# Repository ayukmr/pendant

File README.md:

# pendant

Pendant with a charlieplexed LED matrix using an ATSAMD21.

## Demo

## Schematic

## PCB

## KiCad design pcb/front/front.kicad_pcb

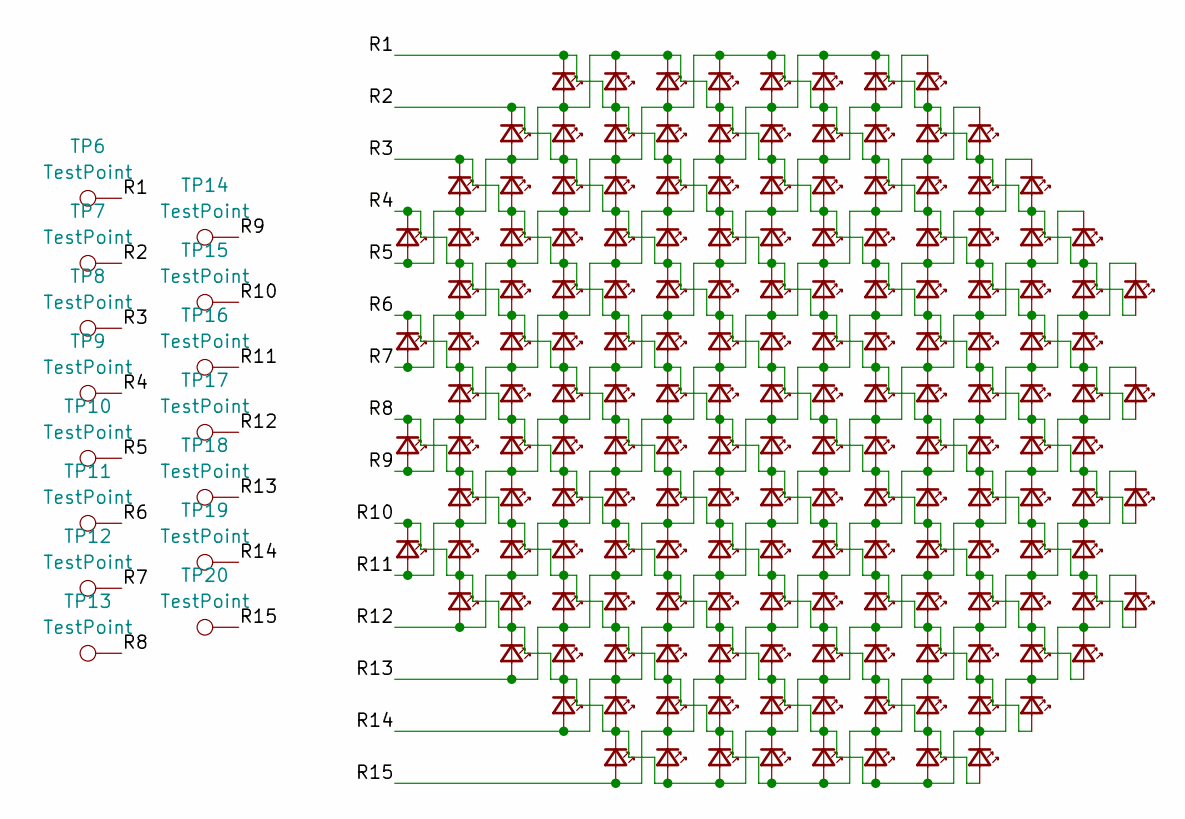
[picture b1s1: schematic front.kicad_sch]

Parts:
D1, D2, D3, D4, D5, D6, D7, D8, D9, D10, D11, D12, D13, D14, D15, D16, D17, D18, D19, D20, D21, D22, D23, D24, D25, D26, D27, D28, D29, D30, D31, D32, D33, D34, D35, D36, D37, D38, D39, D40, D41, D42, D43, D44, D45, D46, D47, D48, D49, D50, D51, D52, D53, D54, D55, D56, D57, D58, D59, D60, D61, D62, D63, D64, D65, D66, D67, D68, D69, D70, D71, D72, D73, D74, D75, D76, D77, D78, D79, D80, D81, D82, D83, D84, D85, D86, D87, D88, D89, D90, D91, D92, D93, D94, D95, D96, D97, D98, D99, D100, D101, D102, D103, D104, D105, D106, D107, D108, D109, D110, D111, D112, D113, D114, D115, D116, D117, D118, D119, D120, D121, D122, D123, D124, D125, D126, D127, D128, D129, D130, D131, D132, D133, D134, D135, D136, D137, D138, D139, D140, D141, D142, D143, D144, D145, D146, D147, D148, D149, D150, D151, D152, D153, D154, D155, D156, D157, D158, D159, D160, D161, D162, D163, D164, D165, D166, D167, D168, D169, D170, D171, D172: LED_Small; LED_0402_1005Metric
TP6, TP7, TP8, TP9, TP10, TP11, TP12, TP13, TP14, TP15, TP16, TP17, TP18, TP19, TP20: TestPoint; Pad_SMD_1.6x1.6

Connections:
/R1: D1.1 (K), D2.2 (A), D11.1 (K), D12.2 (A), D23.1 (K), D24.2 (A), D37.1 (K), D38.2 (A), D51.1 (K), D52.2 (A), D67.1 (K), D68.2 (A), D81.1 (K), D82.2 (A), D97.1 (K), D98.2 (A), D111.1 (K), D112.2 (A), D127.1 (K), D128.2 (A), D141.1 (K), D142.2 (A), TP6.1 (1_1)
/R2: D9.1 (K), D10.2 (A), D21.1 (K), D22.2 (A), D35.1 (K), D36.2 (A), D49.1 (K), D50.2 (A), D65.1 (K), D66.2 (A), D79.1 (K), D80.2 (A), D95.1 (K), D96.2 (A), D109.1 (K), D110.2 (A), D125.1 (K), D126.2 (A), D139.1 (K), D140.2 (A), D153.1 (K), D154.2 (A), TP7.1 (1_1)
/R3: D19.1 (K), D20.2 (A), D33.1 (K), D34.2 (A), D47.1 (K), D48.2 (A), D63.1 (K), D64.2 (A), D77.1 (K), D78.2 (A), D93.1 (K), D94.2 (A), D107.1 (K), D108.2 (A), D123.1 (K), D124.2 (A), D137.1 (K), D138.2 (A), D151.1 (K), D152.2 (A), D163.1 (K), D164.2 (A), TP8.1 (1_1)
/R4: D31.1 (K), D32.2 (A), D45.1 (K), D46.2 (A), D61.1 (K), D62.2 (A), D75.1 (K), D76.2 (A), D91.1 (K), D92.2 (A), D105.1 (K), D106.2 (A), D121.1 (K), D122.2 (A), D135.1 (K), D136.2 (A), D149.1 (K), D150.2 (A), D161.1 (K), D162.2 (A), D171.1 (K), D172.2 (A), TP9.1 (1_1)
/R5: D1.2 (A), D2.1 (K), D3.1 (K), D4.2 (A), D9.2 (A), D10.1 (K), D13.1 (K), D14.2 (A), D19.2 (A), D20.1 (K), D25.1 (K), D26.2 (A), D31.2 (A), D32.1 (K), D39.1 (K), D40.2 (A), D53.1 (K), D54.2 (A), D69.1 (K), D70.2 (A), D83.1 (K), D84.2 (A), D99.1 (K), D100.2 (A), D113.1 (K), D114.2 (A), TP10.1 (1_1)
/R6: D59.1 (K), D60.2 (A), D73.1 (K), D74.2 (A), D89.1 (K), D90.2 (A), D103.1 (K), D104.2 (A), D119.1 (K), D120.2 (A), D133.1 (K), D134.2 (A), D141.2 (A), D142.1 (K), D147.1 (K), D148.2 (A), D153.2 (A), D154.1 (K), D159.1 (K), D160.2 (A), D163.2 (A), D164.1 (K), D169.1 (K), D170.2 (A), D171.2 (A), D172.1 (K), TP11.1 (1_1)
/R7: D3.2 (A), D4.1 (K), D5.1 (K), D6.2 (A), D11.2 (A), D12.1 (K), D15.1 (K), D16.2 (A), D21.2 (A), D22.1 (K), D27.1 (K), D28.2 (A), D33.2 (A), D34.1 (K), D41.1 (K), D42.2 (A), D45.2 (A), D46.1 (K), D55.1 (K), D56.2 (A), D59.2 (A), D60.1 (K), D71.1 (K), D72.2 (A), D85.1 (K), D86.2 (A), TP12.1 (1_1)
/R8: D87.1 (K), D88.2 (A), D101.1 (K), D102.2 (A), D113.2 (A), D114.1 (K), D117.1 (K), D118.2 (A), D127.2 (A), D128.1 (K), D131.1 (K), D132.2 (A), D139.2 (A), D140.1 (K), D145.1 (K), D146.2 (A), D151.2 (A), D152.1 (K), D157.1 (K), D158.2 (A), D161.2 (A), D162.1 (K), D167.1 (K), D168.2 (A), D169.2 (A), D170.1 (K), TP13.1 (1_1)
/R9: D5.2 (A), D6.1 (K), D7.1 (K), D8.2 (A), D13.2 (A), D14.1 (K), D17.1 (K), D18.2 (A), D23.2 (A), D24.1 (K), D29.1 (K), D30.2 (A), D35.2 (A), D36.1 (K), D43.1 (K), D44.2 (A), D47.2 (A), D48.1 (K), D57.1 (K), D58.2 (A), D61.2 (A), D62.1 (K), D73.2 (A), D74.1 (K), D87.2 (A), D88.1 (K), TP14.1 (1_1)
/R10: D85.2 (A), D86.1 (K), D99.2 (A), D100.1 (K), D111.2 (A), D112.1 (K), D115.1 (K), D116.2 (A), D125.2 (A), D126.1 (K), D129.1 (K), D130.2 (A), D137.2 (A), D138.1 (K), D143.1 (K), D144.2 (A), D149.2 (A), D150.1 (K), D155.1 (K), D156.2 (A), D159.2 (A), D160.1 (K), D165.1 (K), D166.2 (A), D167.2 (A), D168.1 (K), TP15.1 (1_1)
/R11: D7.2 (A), D8.1 (K), D15.2 (A), D16.1 (K), D25.2 (A), D26.1 (K), D37.2 (A), D38.1 (K), D49.2 (A), D50.1 (K), D63.2 (A), D64.1 (K), D75.2 (A), D76.1 (K), D89.2 (A), D90.1 (K), D101.2 (A), D102.1 (K), D115.2 (A), D116.1 (K), TP16.1 (1_1)
/R12: D17.2 (A), D18.1 (K), D27.2 (A), D28.1 (K), D39.2 (A), D40.1 (K), D51.2 (A), D52.1 (K), D65.2 (A), D66.1 (K), D77.2 (A), D78.1 (K), D91.2 (A), D92.1 (K), D103.2 (A), D104.1 (K), D117.2 (A), D118.1 (K), D129.2 (A), D130.1 (K), TP17.1 (1_1)
/R13: D29.2 (A), D30.1 (K), D41.2 (A), D42.1 (K), D53.2 (A), D54.1 (K), D67.2 (A), D68.1 (K), D79.2 (A), D80.1 (K), D93.2 (A), D94.1 (K), D105.2 (A), D106.1 (K), D119.2 (A), D120.1 (K), D131.2 (A), D132.1 (K), D143.2 (A), D144.1 (K), TP18.1 (1_1)
/R14: D43.2 (A), D44.1 (K), D55.2 (A), D56.1 (K), D69.2 (A), D70.1 (K), D81.2 (A), D82.1 (K), D95.2 (A), D96.1 (K), D107.2 (A), D108.1 (K), D121.2 (A), D122.1 (K), D133.2 (A), D134.1 (K), D145.2 (A), D146.1 (K), D155.2 (A), D156.1 (K), TP19.1 (1_1)
/R15: D57.2 (A), D58.1 (K), D71.2 (A), D72.1 (K), D83.2 (A), D84.1 (K), D97.2 (A), D98.1 (K), D109.2 (A), D110.1 (K), D123.2 (A), D124.1 (K), D135.2 (A), D136.1 (K), D147.2 (A), D148.1 (K), D157.2 (A), D158.1 (K), D165.2 (A), D166.1 (K), TP20.1 (1_1)

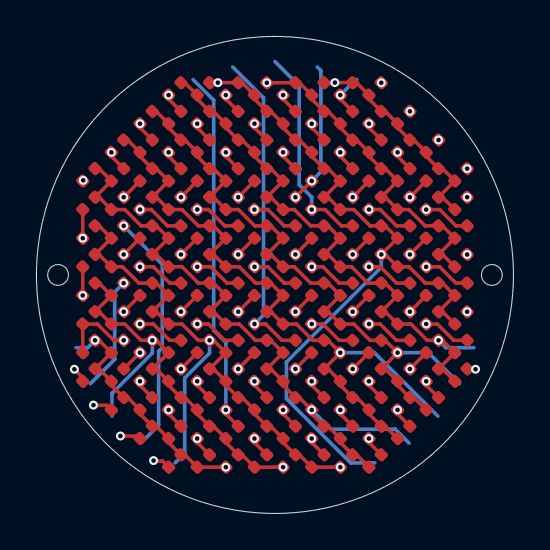
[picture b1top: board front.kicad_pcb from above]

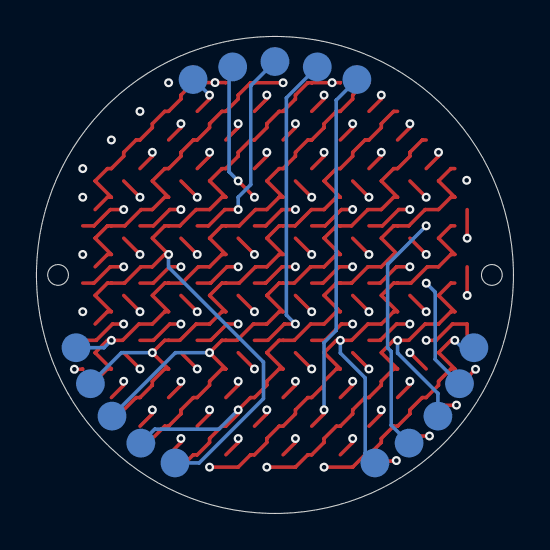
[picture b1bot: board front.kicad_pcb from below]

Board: 4 copper layers, 26.5 x 26.5 mm, 187 parts (15 on the bottom side), 15 nets.

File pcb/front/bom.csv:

Reference,Qty,Value,Footprint,Datasheet,LCSC Part #
"D1,D2,D3,D4,D5,D6,D7,D8,D9,D10,D11,D12,D13,D14,D15,D16,D17,D18,D19,D20,D21,D22,D23,D24,D25,D26,D27,D28,D29,D30,D31,D32,D33,D34,D35,D36,D37,D38,D39,D40,D41,D42,D43,D44,D45,D46,D47,D48,D49,D50,D51,D52,D53,D54,D55,D56,D57,D58,D59,D60,D61,D62,D63,D64,D65,D66,D67,D68,D69,D70,D71,D72,D73,D74,D75,D76,D77,D78,D79,D80,D81,D82,D83,D84,D85,D86,D87,D88,D89,D90,D91,D92,D93,D94,D95,D96,D97,D98,D99,D100,D101,D102,D103,D104,D105,D106,D107,D108,D109,D110,D111,D112,D113,D114,D115,D116,D117,D118,D119,D120,D121,D122,D123,D124,D125,D126,D127,D128,D129,D130,D131,D132,D133,D134,D135,D136,D137,D138,D139,D140,D141,D142,D143,D144,D145,D146,D147,D148,D149,D150,D151,D152,D153,D154,D155,D156,D157,D158,D159,D160,D161,D162,D163,D164,D165,D166,D167,D168,D169,D170,D171,D172",172,LED_Small,Project:LED_0402_1005Metric,~,C397045

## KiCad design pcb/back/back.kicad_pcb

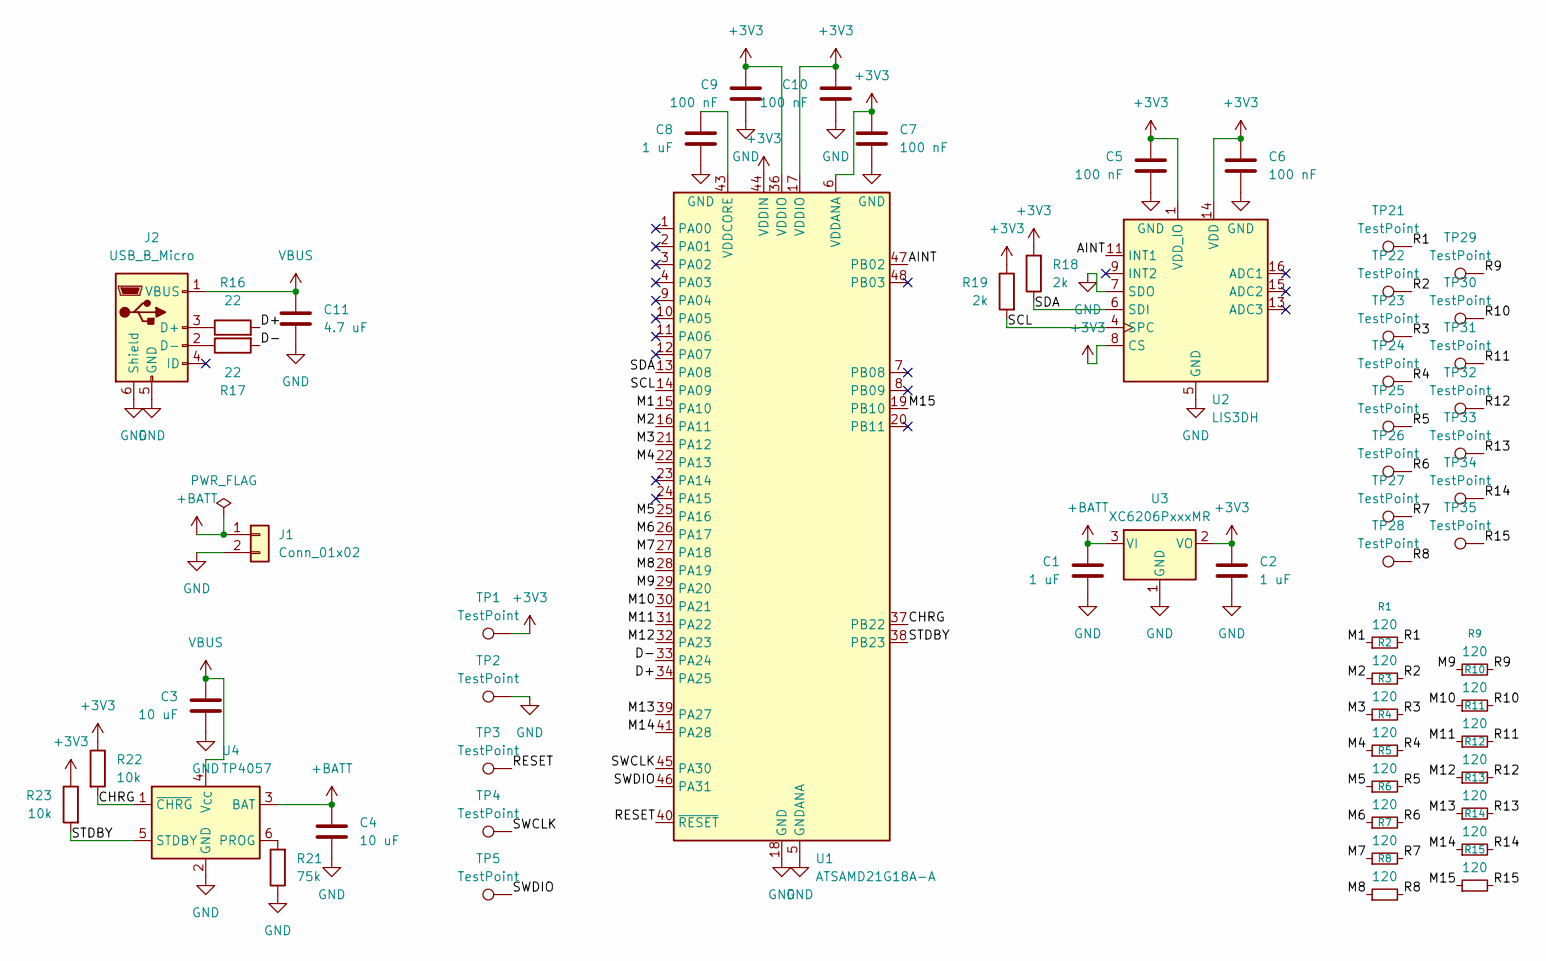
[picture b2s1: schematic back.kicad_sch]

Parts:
C1, C2, C8: 1 uF; C_0402_1005Metric
C3, C4: 10 uF; C_0603_1608Metric
C5, C6, C7, C9, C10: 100 nF; C_0402_1005Metric
C11: 4.7 uF; C_0603_1608Metric
J1: Conn_01x02; JST_SH_SM02B-SRSS-TB_1x02-1MP_P1.00mm_Horizontal
J2: USB_B_Micro; MICRO-USB-SMD_47346-0001
R1, R2, R3, R4, R5, R6, R7, R8, R9, R10, R11, R12, R13, R14, R15: 120; R_0402_1005Metric
R16, R17: 22; R_0402_1005Metric
R18, R19: 2k; R_0402_1005Metric
R21: 75k; R_0402_1005Metric
R22, R23: 10k; R_0402_1005Metric
TP1, TP2, TP3, TP4, TP5: TestPoint; Pad_SMD_1.5x1.5
TP21, TP22, TP23, TP24, TP25, TP26, TP27, TP28, TP29, TP30, TP31, TP32, TP33, TP34, TP35: TestPoint; THT_D0.8_Pad1.6x1.6
U1: ATSAMD21G18A-A; TQFP-48_7x7mm_P0.5mm
U2: LIS3DH; LGA-16_3x3mm_P0.5mm_LayoutBorder3x5y
U3: XC6206PxxxMR; SOT-23-3
U4: TP4057; TSOT-23-6

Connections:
+3V3: C2.1, C5.2, C6.2, C7.1, C9.2, C10.2, R18.2, R19.1, R22.1, R23.1, TP1.1 (1_1), U1.6 (VDDANA), U1.17 (VDDIO), U1.36 (VDDIO), U1.44 (VDDIN), U2.1 (VDD_IO), U2.8 (CS), U2.14 (VDD), U3.2 (VO)
+BATT: C1.1, C4.1, J1.1, U3.3 (VI), U4.3 (BAT)
/AINT: U1.47 (PB02), U2.11 (INT1)
/CHRG: R22.2, U1.37 (PB22), U4.1 (~CHRG)
/D+: R16.2, U1.34 (PA25)
/D-: R17.2, U1.33 (PA24)
/M1: R1.1, U1.15 (PA10)
/M2: R2.1, U1.16 (PA11)
/M3: R3.1, U1.21 (PA12)
/M4: R4.1, U1.22 (PA13)
/M5: R5.1, U1.25 (PA16)
/M6: R6.1, U1.26 (PA17)
/M7: R7.1, U1.27 (PA18)
/M8: R8.1, U1.28 (PA19)
/M9: R9.1, U1.29 (PA20)
/M10: R10.1, U1.30 (PA21)
/M11: R11.1, U1.31 (PA22)
/M12: R12.1, U1.32 (PA23)
/M13: R13.1, U1.39 (PA27)
/M14: R14.1, U1.41 (PA28)
/M15: R15.1, U1.19 (PB10)
/R1: R1.2, TP21.1 (1_1)
/R2: R2.2, TP22.1 (1_1)
/R3: R3.2, TP23.1 (1_1)
/R4: R4.2, TP24.1 (1_1)
/R5: R5.2, TP25.1 (1_1)
/R6: R6.2, TP26.1 (1_1)
/R7: R7.2, TP27.1 (1_1)
/R8: R8.2, TP28.1 (1_1)
/R9: R9.2, TP29.1 (1_1)
/R10: R10.2, TP30.1 (1_1)
/R11: R11.2, TP31.1 (1_1)
/R12: R12.2, TP32.1 (1_1)
/R13: R13.2, TP33.1 (1_1)
/R14: R14.2, TP34.1 (1_1)
/R15: R15.2, TP35.1 (1_1)
/RESET: TP3.1 (1_1), U1.40 (~RESET)
/SCL: R19.2, U1.14 (PA09), U2.4 (SPC)
/SDA: R18.1, U1.13 (PA08), U2.6 (SDI)
/STDBY: R23.2, U1.38 (PB23), U4.5 (STDBY)
/SWCLK: TP4.1 (1_1), U1.45 (PA30)
/SWDIO: TP5.1 (1_1), U1.46 (PA31)
GND: C1.2, C2.2, C3.2, C4.2, C5.1, C6.1, C7.2, C8.2, C9.1, C10.1, C11.1, J1.2, J2.5 (GND), J2.6 (Shield), R21.1, TP2.1 (1_1), U1.5 (GNDANA), U1.18 (GND), U1.35 (GND), U1.42 (GND), U2.5 (GND), U2.7 (SDO), U2.10 (GND), U2.12 (GND), U3.1 (GND), U4.2 (GND)
unnamed: J2.3 (D+), R16.1
unnamed: J2.2 (D-), R17.1
unnamed: C8.1, U1.43 (VDDCORE)
unnamed: R21.2, U4.6 (PROG)
VBUS: C3.1, C11.2, J2.1 (VBUS), U4.4 (V_{CC})

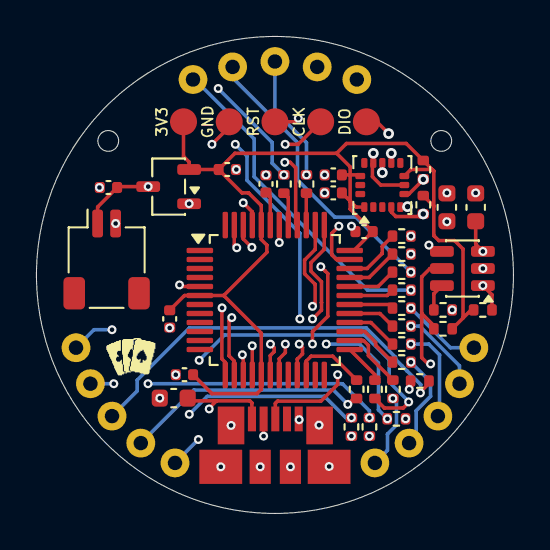
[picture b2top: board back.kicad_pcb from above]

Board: 4 copper layers, 26.5 x 26.5 mm, 59 parts (0 on the bottom side), 48 nets.

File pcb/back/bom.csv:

Reference,Qty,Value,Footprint,Datasheet,LCSC Part #
"C1,C2,C8",3,1 µF,Capacitor_SMD:C_0402_1005Metric,~,C52923
"C3,C4",2,10 µF,Capacitor_SMD:C_0603_1608Metric,~,C19702
"C5,C6,C7,C9,C10",5,100 nF,Capacitor_SMD:C_0402_1005Metric,~,C1525
C11,1,4.7 µF,Capacitor_SMD:C_0603_1608Metric,~,C19666
J1,1,Conn_01x02,Connector_JST:JST_SH_SM02B-SRSS-TB_1x02-1MP_P1.00mm_Horizontal,~,C160402
J2,1,USB_B_Micro,Project:MICRO-USB-SMD_47346-0001,~,C132560
"R1,R2,R3,R4,R5,R6,R7,R8,R9,R10,R11,R12,R13,R14,R15",15,120 Ω,Resistor_SMD:R_0402_1005Metric,~,C25079
"R16,R17",2,22 Ω,Resistor_SMD:R_0402_1005Metric,~,C25092
"R18,R19",2,2k Ω,Resistor_SMD:R_0402_1005Metric,~,C4109
"R22,R23",2,10k Ω,Resistor_SMD:R_0402_1005Metric,~,C25744
R21,1,75k Ω,Resistor_SMD:R_0402_1005Metric,~,C25798
U1,1,ATSAMD21G18A-A,Package_QFP:TQFP-48_7x7mm_P0.5mm,http://ww1.microchip.com/downloads/en/DeviceDoc/SAM_D21_DA1_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,C619067
U2,1,LIS3DH,Package_LGA:LGA-16_3x3mm_P0.5mm_LayoutBorder3x5y,https://www.st.com/resource/en/datasheet/cd00274221.pdf,LIS3DHTR
U3,1,XC6206PxxxMR,Package_TO_SOT_SMD:SOT-23-3,https://www.torexsemi.com/file/xc6206/XC6206.pdf,C5446
U4,1,TP4057,Package_TO_SOT_SMD:TSOT-23-6,http://toppwr.com/uploadfile/file/20230304/640302a47b738.pdf,C12044

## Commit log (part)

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2026-03-07 Initialize repo
2026-03-09 Add license
2026-03-11 Revise PCB
2026-05-15 Format schematic
2026-05-17 Update gitignore
2026-05-17 Update LEDs
2026-05-25 Check values
2026-05-25 Adjust SWD pad pitch
2026-05-26 Split PCB sides
2026-05-26 Update accelerometer
2026-05-26 Add tooling holes
2026-05-27 Format schematics
2026-05-28 Additional format
2026-05-29 Use 2k I2C resistors
2026-06-02 Update LED resistors
2026-06-02 Update LED part
